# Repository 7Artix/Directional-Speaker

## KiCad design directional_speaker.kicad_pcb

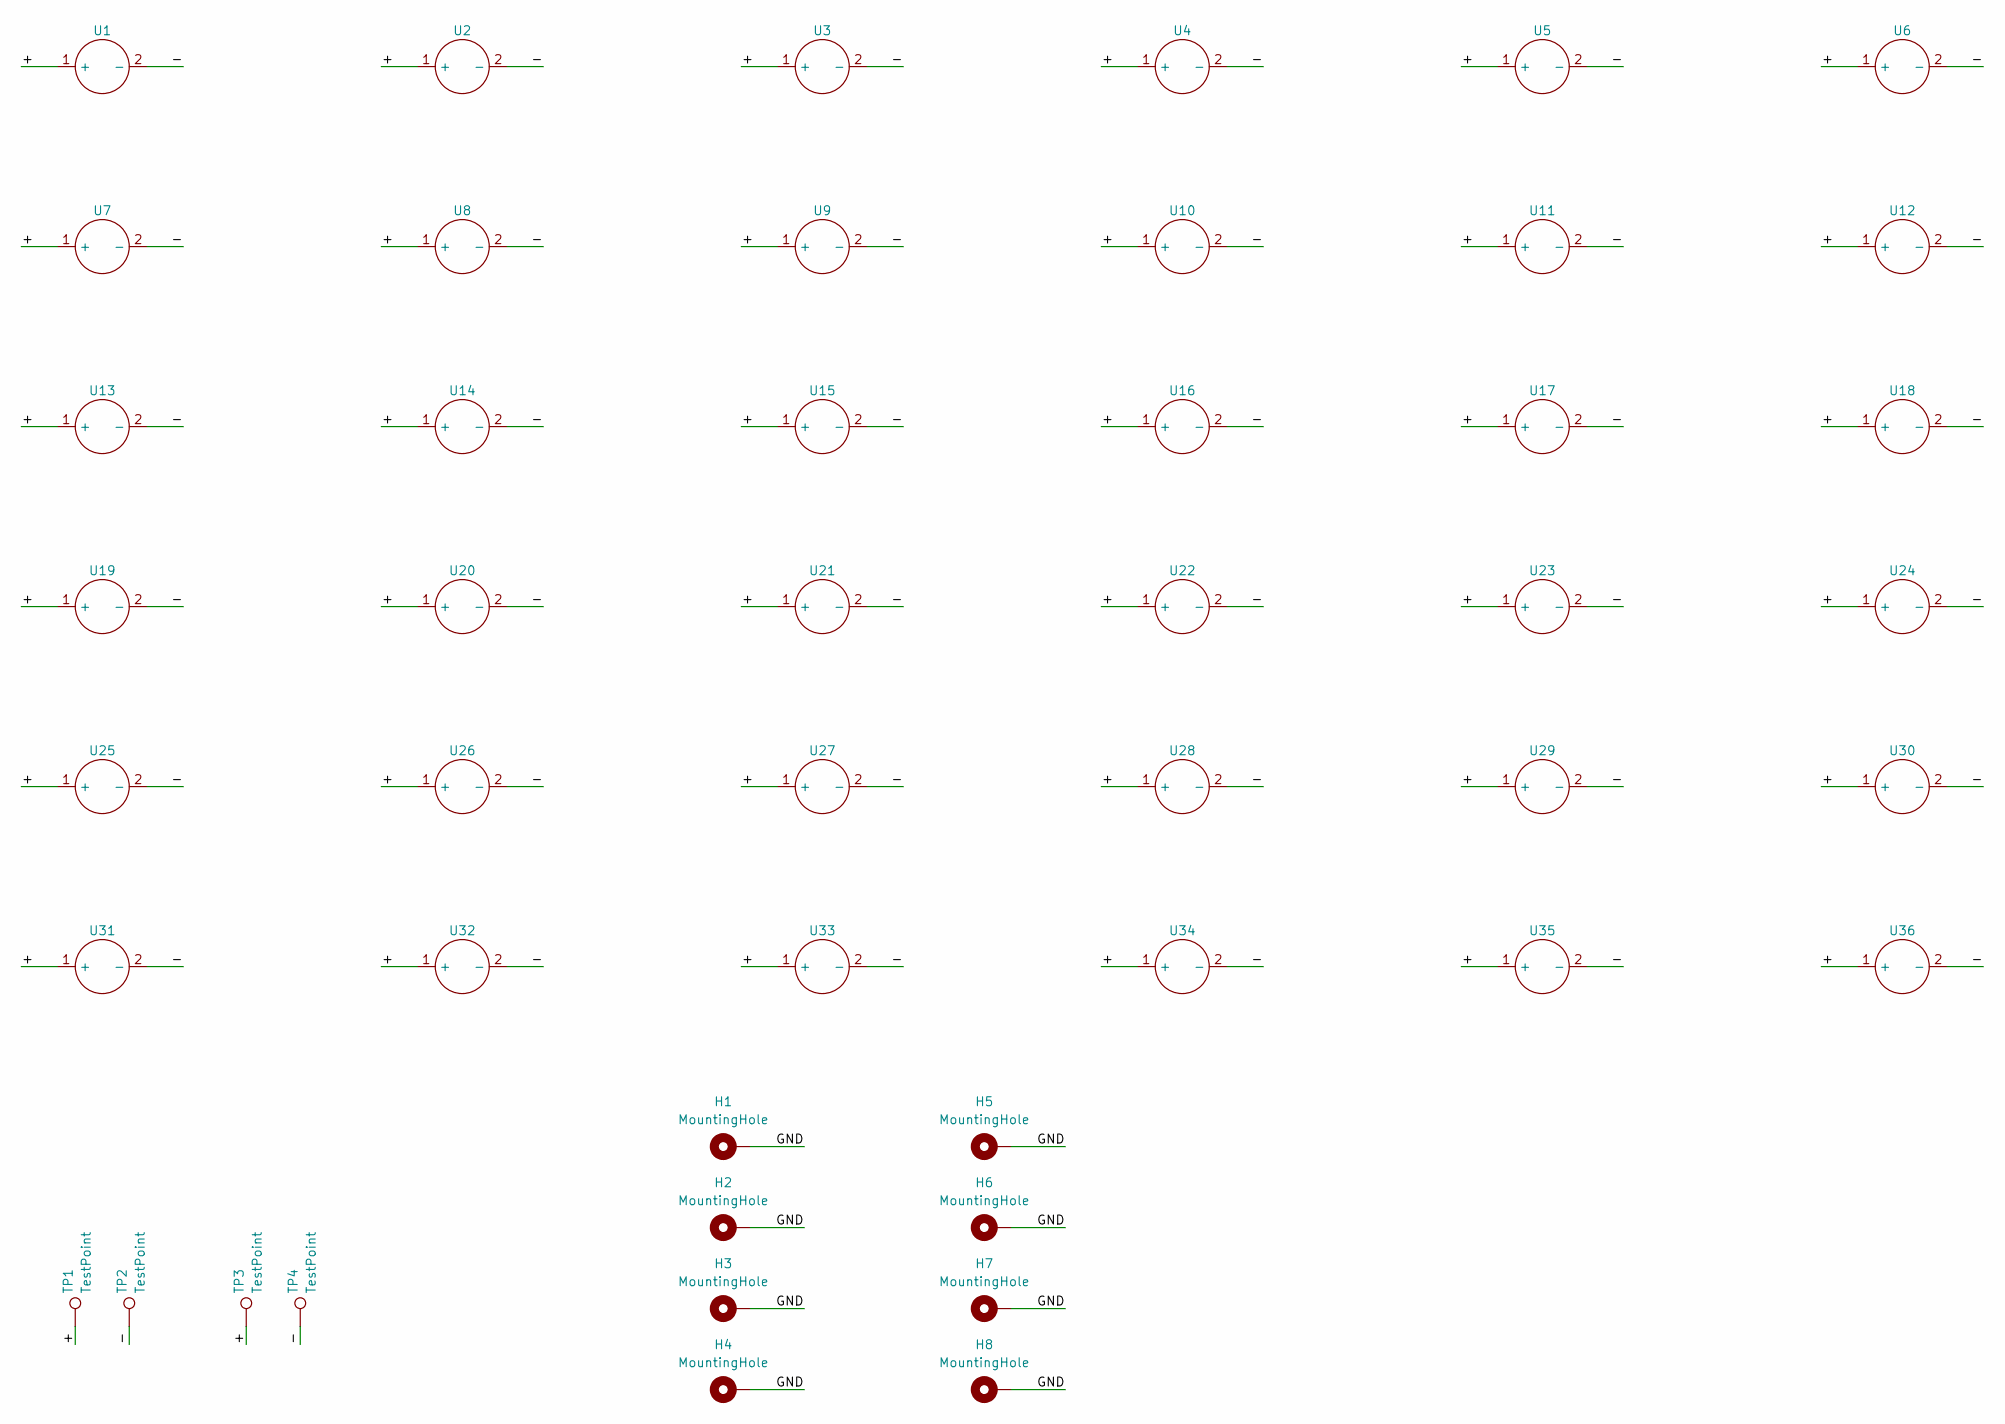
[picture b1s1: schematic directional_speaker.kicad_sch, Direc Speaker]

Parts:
H1, H2, H3, H4, H5, H6, H7, H8: MountingHole; MountingHole_3.2mm_M3_Pad
TP1, TP3: TestPoint; REC_PAD_3x5_OUTLINE
TP2, TP4: TestPoint; REC_PAD_3x5
U1, U2, U3, U4, U5, U6, U7, U8, U9, U10, U11, U12, U13, U14, U15, U16, U17, U18, U19, U20, U21, U22, U23, U24, U25, U26, U27, U28, U29, U30, U31, U32, U33, U34, U35, U36: Ultrasound_16mm

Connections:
/+: TP1.1, TP3.1, U1.1 (+), U2.1 (+), U3.1 (+), U4.1 (+), U5.1 (+), U6.1 (+), U7.1 (+), U8.1 (+), U9.1 (+), U10.1 (+), U11.1 (+), U12.1 (+), U13.1 (+), U14.1 (+), U15.1 (+), U16.1 (+), U17.1 (+), U18.1 (+), U19.1 (+), U20.1 (+), U21.1 (+), U22.1 (+), U23.1 (+), U24.1 (+), U25.1 (+), U26.1 (+), U27.1 (+), U28.1 (+), U29.1 (+), U30.1 (+), U31.1 (+), U32.1 (+), U33.1 (+), U34.1 (+), U35.1 (+), U36.1 (+)
/-: TP2.1, TP4.1, U1.2 (-), U2.2 (-), U3.2 (-), U4.2 (-), U5.2 (-), U6.2 (-), U7.2 (-), U8.2 (-), U9.2 (-), U10.2 (-), U11.2 (-), U12.2 (-), U13.2 (-), U14.2 (-), U15.2 (-), U16.2 (-), U17.2 (-), U18.2 (-), U19.2 (-), U20.2 (-), U21.2 (-), U22.2 (-), U23.2 (-), U24.2 (-), U25.2 (-), U26.2 (-), U27.2 (-), U28.2 (-), U29.2 (-), U30.2 (-), U31.2 (-), U32.2 (-), U33.2 (-), U34.2 (-), U35.2 (-), U36.2 (-)
/GND: H1.1, H2.1, H3.1, H4.1, H5.1, H6.1, H7.1, H8.1

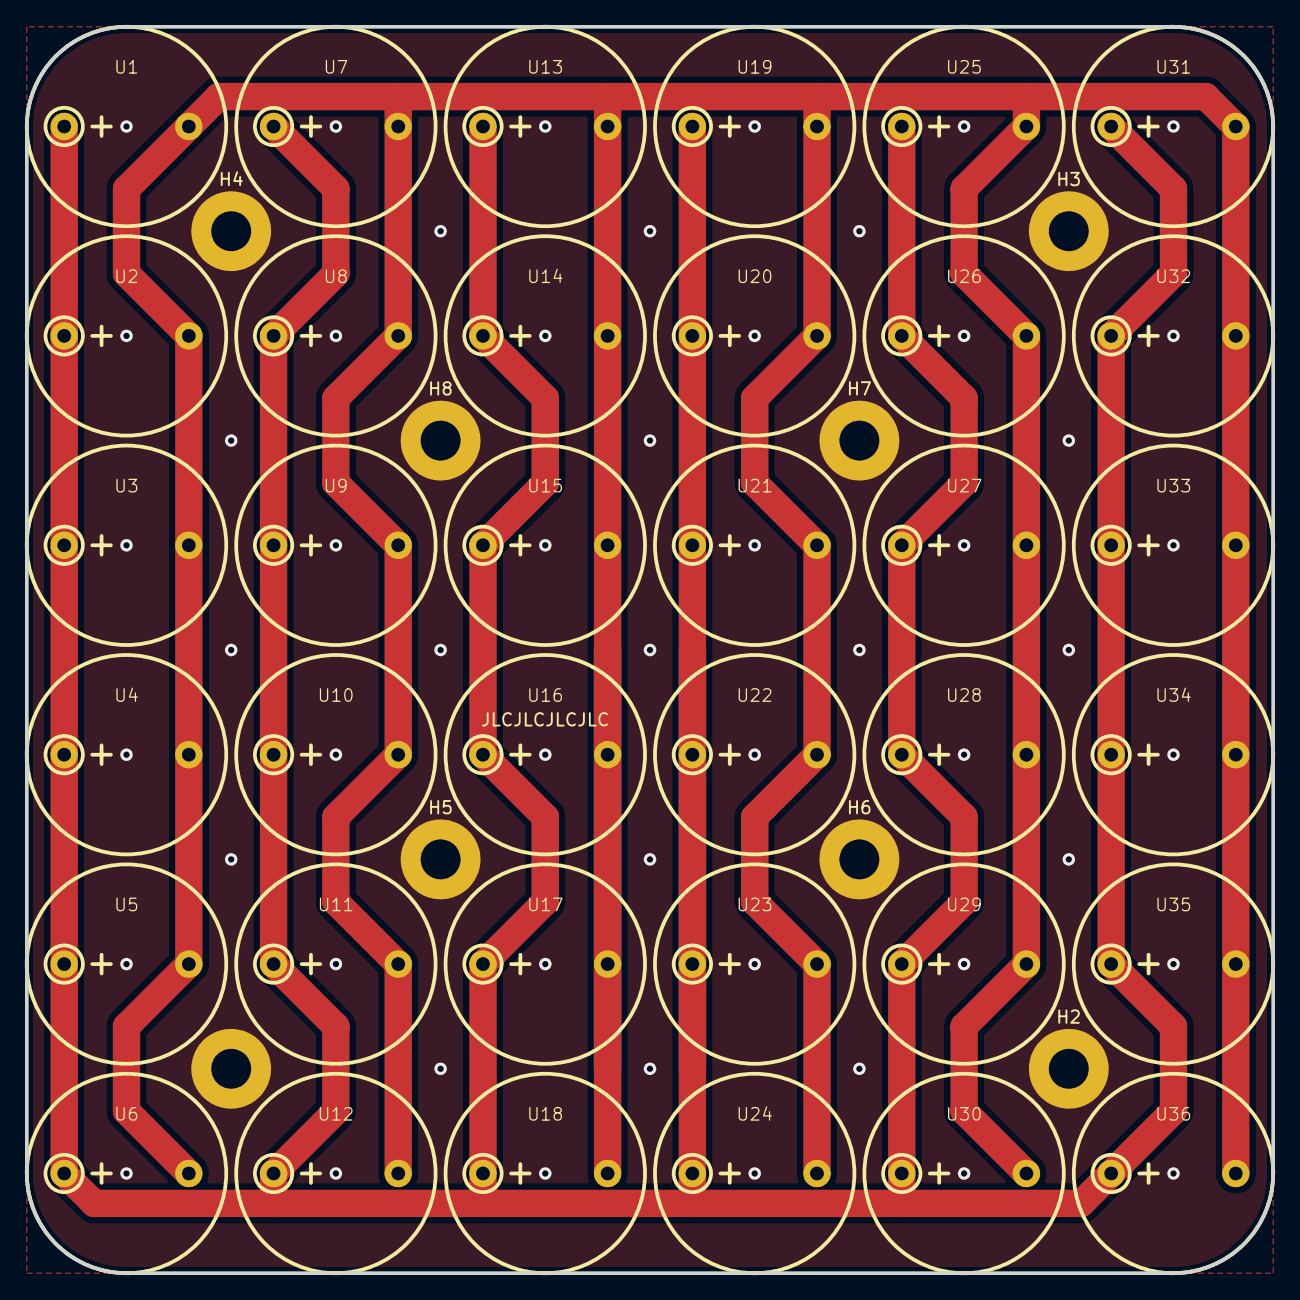
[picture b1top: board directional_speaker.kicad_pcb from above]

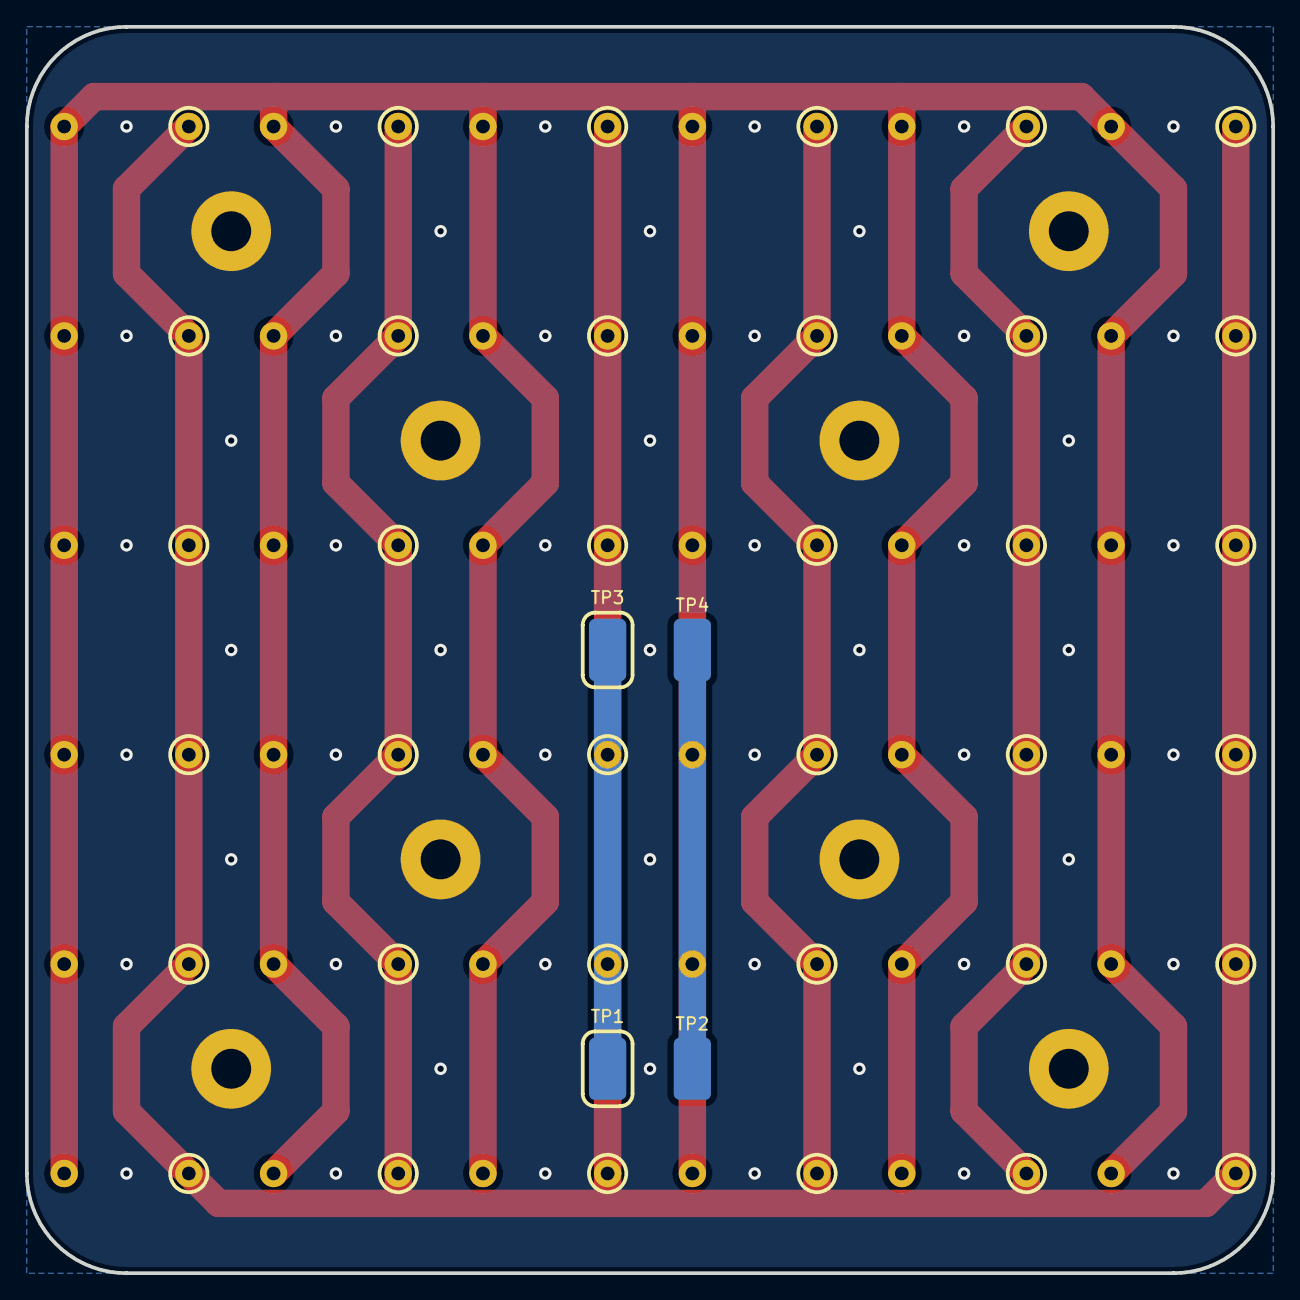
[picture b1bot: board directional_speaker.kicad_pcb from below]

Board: 2 copper layers, 100.0 x 100.0 mm, 48 parts (4 on the bottom side), 3 nets.

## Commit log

2025-08-21 Files updated
